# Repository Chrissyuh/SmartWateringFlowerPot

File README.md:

# Self-Watering Flower Pot V2

Custom ESP32-S3 controller hardware and bring-up firmware for a self-watering flower pot prototype.

This repository contains the KiCad design files, generated fabrication outputs, mechanical STEP exports, board renders, BOM notes, bring-up reports, and the first safe test firmware used on the assembled Board A prototype.

## Current Status

- Board A cost-down prototype has been fabricated and hand assembled for bring-up.
- USB-C power, 3.3 V regulator, ESP32-S3 native USB flashing, status LEDs, moisture ADC, and pump-gate bring-up checks have been tested.
- Current firmware is a supervised pump-test build with adjustable manual pump pulses and a hard 2 second firmware maximum.
- Board B UI daughterboard files remain in the repository as a deferred optional design.
- The cost-down Board A fabrication package is available in `fabrication/board_a_cost_down/`.

## Hardware Overview

Board A is the main controller board:

- ESP32-S3-WROOM-1-N8 module
- USB-C 5 V input
- AP63203 buck regulator for the 3.3 V logic rail
- Capacitive soil moisture sensor input on `J3`
- AO3400A low-side pump MOSFET footprint with gate resistor and pulldown
- SS34-style pump flyback diode
- Red error LED and green status LED
- Optional reservoir switch and flow pulse pads
- Debug/programming backup header `J7`
- Test points for rails and key signals

Board B is a deferred UI daughterboard concept with OLED/encoder support.

## Firmware

The current bring-up firmware lives in `firmware/testcode1/`.

It hosts a local Wi-Fi access point and web page:

- SSID: `FlowerPot-testcode1`
- Password: `flowerpot1`
- URL: `http://192.168.4.1`

The page shows moisture ADC readings, rolling average, min/max/span, rough wetness band, collapsible charts, deep ESP diagnostics, optional input short status, flow pulse count, AP-client/session counters, Wi-Fi settings, LED test buttons, session JSON export, diagnostics JSON export, and a supervised adjustable pump test button. The firmware also prints USB serial UI hints so the Windows helper in `firmware/testcode1/tools/` can open the best available UI URL from a data-cable connection.

Important safety rule: this is not autonomous watering firmware. The pump button requires a browser warning acknowledgement, and the firmware caps each pump run at 2000 ms.

## Repository Map

- `SmartWateringFlowerPot.kicad_pro`, `.kicad_sch`, `.kicad_pcb` - Board A KiCad project
- `board_b_ui/` - deferred UI board KiCad project
- `firmware/testcode1/` - PlatformIO bring-up firmware
- `docs/` - design notes, pinout, BOM notes, bring-up checklist, and hardening review
- `reports/` - saved ERC/DRC and audit reports
- `outputs/` - schematic PDFs, routing PDFs/SVGs, reference images, and 3D renders
- `fabrication/` - Gerbers, drill files, BOM CSVs, and fab zips
- `mechanical/` - STEP exports for enclosure/mechanical fit checks
- `CODEX_HANDOVER.md` - detailed project history and design context

## Bring-Up Notes

Before connecting a pump:

- Verify `+5V`, `+3V3`, and `GND`.
- Confirm there are no rail shorts.
- Confirm the ESP32 flashes over USB.
- Confirm `PUMP_GATE` remains LOW during boot/reset.
- Test the MOSFET gate with the pump disconnected.
- Use short, supervised pump tests only after the MOSFET and flyback diode are verified. Do not run the pump from a laptop USB port.

The moisture connector `J3` board order is:

```text
3V3  GND  SIG
```

The common capacitive sensor mapping is:

```text
VCC -> +3V3
GND -> GND
AOUT -> SIG
```

## Build Firmware

From `firmware/testcode1/`:

```powershell
python -m platformio run
python -m platformio run --target upload
```

The current `platformio.ini` targets the ESP32-S3 over `COM3`; change the port if your machine enumerates it differently.

## KiCad Checks

KiCad 9 is expected. If `kicad-cli` is on your PATH:

```powershell
kicad-cli sch erc --format report --output reports/erc.txt SmartWateringFlowerPot.kicad_sch
kicad-cli pcb drc --format report --output reports/drc.txt SmartWateringFlowerPot.kicad_pcb
```

KiCad GUI remains the source of truth for visual PCB edits.

## License

This project is released under the MIT License. See `LICENSE`.

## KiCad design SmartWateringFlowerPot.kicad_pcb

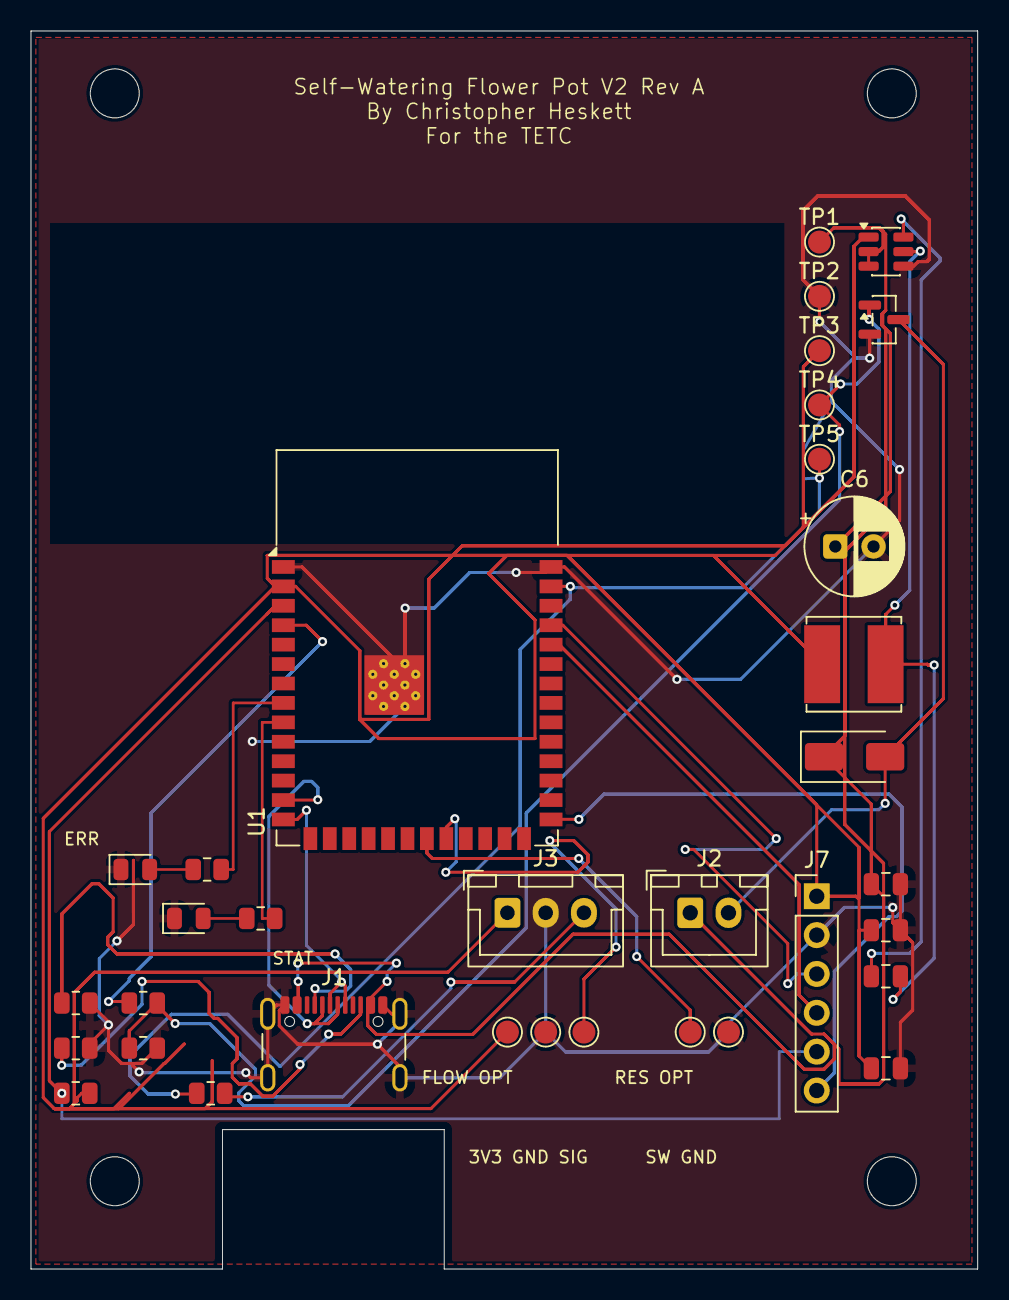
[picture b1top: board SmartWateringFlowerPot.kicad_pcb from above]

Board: 2 copper layers, 61.9 x 80.9 mm, 39 parts (1 on the bottom side), 24 nets.

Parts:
C1: 10uF 10V X7R input; C_0805_2012Metric
C2, C5: 22uF 6.3V X7R output; C_0805_2012Metric
C3: 100nF 10V BST; C_0805_2012Metric
C4: 100nF ADC filter DNP; C_0805_2012Metric
C6: 100uF 10V pump bulk; CP_Radial_D6.3mm_P2.50mm
D1: SS34 flyback; D_SMA
D2: ERROR red; LED_0805_2012Metric
D3: STATUS green; LED_0805_2012Metric
H1, H2, H3, H4: M3 mounting hole; MountingHole_3.2mm_M3
J1: USB-C 5V + USB2; USB_C_Receptacle_GCT_USB4105-xx-A_16P_TopMnt_Horizontal
J2: PUMP 5V; JST_XH_B2B-XH-A_1x02_P2.50mm_Vertical
J3: MOISTURE; JST_XH_B3B-XH-A_1x03_P2.50mm_Vertical
J7: DEBUG 3V3/GND/TX/RX/EN/BOOT; PinHeader_1x06_P2.54mm_Vertical
L1: 3.9uH shielded >=3A Isat; L_Bourns_SRN6045TA
Q1: AO3400A; SOT-23
R1: 5.1k CC1; R_0805_2012Metric
R2: 5.1k CC2; R_0805_2012Metric
R3: 10k EN pullup; R_0805_2012Metric
R4: 220R gate; R_0805_2012Metric
R5: 100k pulldown; R_0805_2012Metric
R10: 1k ADC series; R_0805_2012Metric
R11: 330R error LED; R_0805_2012Metric
R12: 330R status LED; R_0805_2012Metric
TP1: +5V TP; TestPoint_Pad_D1.5mm
TP2: GND TP; TestPoint_Pad_D1.5mm
TP3: +3V3 TP; TestPoint_Pad_D1.5mm
TP4: PUMP_GATE TP; TestPoint_Pad_D1.5mm
TP5: MOISTURE_ADC TP; TestPoint_Pad_D1.5mm
TP6: RESERVOIR_SW optional pad; TestPoint_Pad_D1.5mm
TP7, TP9: OPT_GND pad; TestPoint_Pad_D1.5mm
TP8: OPT_3V3 pad; TestPoint_Pad_D1.5mm
TP10: FLOW_PULSE optional pad; TestPoint_Pad_D1.5mm
U1: ESP32-S3-WROOM-1-N8; ESP32-S3-WROOM-1
U2: AP63203WU-7; TSOT-23-6

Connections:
+3V3: C2.1, C5.1, J3.1, J7.1, L1.1, R3.2, TP3.1, TP8.1, U1.2 (3V3), U2.1 (FB)
+5V: C1.1, C6.1, D1.1 (K), J1.A4 (VBUS), J1.A9 (VBUS), J1.B4 (VBUS), J1.B9 (VBUS), J2.1, TP1.1, U2.2 (EN), U2.3 (IN)
/ERROR_LED: R11.1, U1.8 (IO15)
/ERR_LED_A: D2.2, R11.2
/FLOW_PULSE: TP10.1, U1.22 (IO14)
/RESERVOIR_SW: TP6.1, U1.21 (IO13)
/STATUS_LED: R12.1, U1.9 (IO16)
/STAT_LED_A: D3.2, R12.2
GND: C1.2, C2.2, C4.2, C5.2, C6.2, D2.1, D3.1, J1.A1 (GND), J1.A12 (GND), J1.B1 (GND), J1.B12 (GND), J1.S1 (SHIELD), J3.2, J7.2, Q1.2 (S), R1.2, R2.2, R5.2, TP2.1, TP7.1, TP9.1, U1.1 (GND), U1.40 (GND), U1.41 (GND), U2.4 (GND)
unnamed: D1.2 (A), J2.2, Q1.3 (D)
unnamed: J1.A5 (CC1), R1.1
unnamed: J1.B5 (CC2), R2.1
unnamed: J3.3, R10.2
unnamed: J7.3, U1.37 (TXD0)
unnamed: J7.4, U1.36 (RXD0)
unnamed: J7.5, R3.1, U1.3 (EN)
unnamed: J7.6, U1.27 (IO0)
unnamed: Q1.1 (G), R4.2, R5.1, TP4.1
unnamed: C4.1, R10.1, TP5.1, U1.39 (IO1)
unnamed: R4.1, U1.4 (IO4)
unnamed: J1.A6 (D+), J1.B6 (D+), U1.14 (USB_D+)
unnamed: J1.A7 (D-), J1.B7 (D-), U1.13 (USB_D-)
unnamed: C3.1, U2.6 (BST)
unnamed: C3.2, L1.2, U2.5 (SW)

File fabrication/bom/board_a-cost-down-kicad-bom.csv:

"Refs","Value","Footprint","Qty","DNP"
"C1","10uF 10V X7R input","Capacitor_SMD:C_0805_2012Metric","1",""
"C2","22uF 6.3V X7R output","Capacitor_SMD:C_0805_2012Metric","1",""
"C3","100nF 10V BST","Capacitor_SMD:C_0805_2012Metric","1",""
"C5","22uF 6.3V X7R output","Capacitor_SMD:C_0805_2012Metric","1",""
"C6","100uF 10V pump bulk","Capacitor_THT:CP_Radial_D6.3mm_P2.50mm","1",""
"D1","SS34 flyback","Diode_SMD:D_SMA","1",""
"D2","ERROR red","LED_SMD:LED_0805_2012Metric","1",""
"D3","STATUS green","LED_SMD:LED_0805_2012Metric","1",""
"J1","USB-C 5V + USB2","Connector_USB:USB_C_Receptacle_GCT_USB4105-xx-A_16P_TopMnt_Horizontal","1",""
"J2","PUMP 5V","Connector_JST:JST_XH_B2B-XH-A_1x02_P2.50mm_Vertical","1",""
"J3","MOISTURE","Connector_JST:JST_XH_B3B-XH-A_1x03_P2.50mm_Vertical","1",""
"J7","DEBUG 3V3/GND/TX/RX/EN/BOOT","Connector_PinHeader_2.54mm:PinHeader_1x06_P2.54mm_Vertical","1",""
"L1","3.9uH shielded >=3A Isat","Inductor_SMD:L_Bourns_SRN6045TA","1",""
"Q1","AO3400A","Package_TO_SOT_SMD:SOT-23","1",""
"R1","5.1k CC1","Resistor_SMD:R_0805_2012Metric","1",""
"R2","5.1k CC2","Resistor_SMD:R_0805_2012Metric","1",""
"R3","10k EN pullup","Resistor_SMD:R_0805_2012Metric","1",""
"R4","220R gate","Resistor_SMD:R_0805_2012Metric","1",""
"R5","100k pulldown","Resistor_SMD:R_0805_2012Metric","1",""
"R10","1k ADC series","Resistor_SMD:R_0805_2012Metric","1",""
"R11","330R error LED","Resistor_SMD:R_0805_2012Metric","1",""
"R12","330R status LED","Resistor_SMD:R_0805_2012Metric","1",""
"TP1","+5V TP","TestPoint:TestPoint_Pad_D1.5mm","1",""
"TP2","GND TP","TestPoint:TestPoint_Pad_D1.5mm","1",""
"TP3","+3V3 TP","TestPoint:TestPoint_Pad_D1.5mm","1",""
"TP4","PUMP_GATE TP","TestPoint:TestPoint_Pad_D1.5mm","1",""
"TP5","MOISTURE_ADC TP","TestPoint:TestPoint_Pad_D1.5mm","1",""
"U1","ESP32-S3-WROOM-1-N8","RF_Module:ESP32-S3-WROOM-1","1",""
"U2","AP63203WU-7","Package_TO_SOT_SMD:TSOT-23-6","1",""

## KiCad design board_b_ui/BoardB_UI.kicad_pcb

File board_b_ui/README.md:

# Board B UI Daughterboard

Board B connects to Board A J6 through J1 with the same pin order:

1. `+3V3`
2. `GND`
3. `SDA`
4. `SCL`
5. `ENC_A`
6. `ENC_B`
7. `ENC_SW`
8. `ERROR_LED`
9. `STATUS_LED`

The OLED header target is the common 4-pin SSD1306 I2C module order `GND`, `VCC/3V3`, `SCL`, `SDA`. Verify the actual module pin order before fabrication.

The PCB outline is 64 mm x 38 mm with M2.5 non-plated mounting holes. The front side is the user-facing panel with the OLED header/module outline, EC11 encoder footprint, error/status LEDs, and labels. The 9-pin JST-XH cable connector and the support R/C parts are on the back side.

Board B has explicit routed copper for every net plus front/back `GND` zones. Refill zones in KiCad with `B` after manual edits and rerun DRC before fabrication.

Current review/fabrication artifacts:

- Checks: `reports/erc-board-b-front-panel.txt`, `reports/drc-board-b-front-panel.txt`, and `reports/drc-board-b-front-panel-parity.txt`
- Routing review: `outputs/BoardB_UI_routing.svg` and `outputs/BoardB_UI_routing.pdf`
- Schematic PDF: `outputs/BoardB_UI_schematic.pdf`
- STEP: `mechanical/BoardB_UI.step`
- Gerbers and drills: `../fabrication/board_b/`

The KiCad footprint references an EC11 3D model under `Rotary_Encoder.3dshapes`. This KiCad install does not include that model, so the STEP export may omit the encoder body even though the footprint, holes, and courtyard are present.

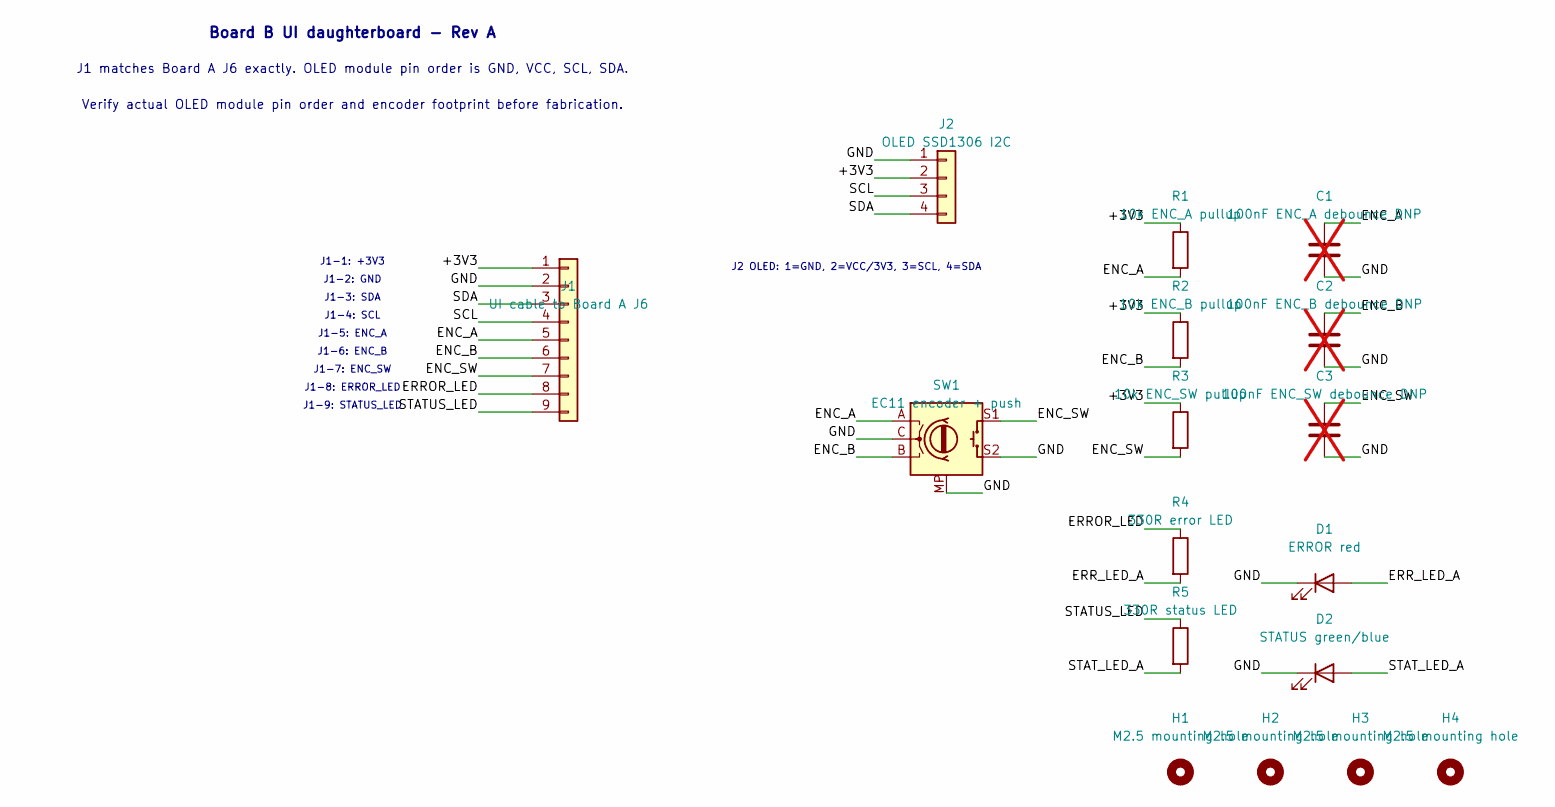
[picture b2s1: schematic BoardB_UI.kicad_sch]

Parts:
C1: 100nF ENC_A debounce DNP; C_0805_2012Metric; not fitted
C2: 100nF ENC_B debounce DNP; C_0805_2012Metric; not fitted
C3: 100nF ENC_SW debounce DNP; C_0805_2012Metric; not fitted
D1: ERROR red; LED_0805_2012Metric
D2: STATUS green/blue; LED_0805_2012Metric
H1, H2, H3, H4: M2.5 mounting hole; MountingHole_2.7mm_M2.5
J1: UI cable to Board A J6; JST_XH_S9B-XH-A_1x09_P2.50mm_Horizontal
J2: OLED SSD1306 I2C; PinHeader_1x04_P2.54mm_Vertical
R1: 10k ENC_A pullup; R_0805_2012Metric
R2: 10k ENC_B pullup; R_0805_2012Metric
R3: 10k ENC_SW pullup; R_0805_2012Metric
R4: 330R error LED; R_0805_2012Metric
R5: 330R status LED; R_0805_2012Metric
SW1: EC11 encoder + push; RotaryEncoder_Alps_EC11E-Switch_Vertical_H20mm

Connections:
/+3V3: J1.1, J2.2, R1.1, R2.1, R3.1
/ENC_A: C1.1, J1.5, R1.2, SW1.A
/ENC_B: C2.1, J1.6, R2.2, SW1.B
/ENC_SW: C3.1, J1.7, R3.2, SW1.S1
/ERROR_LED: J1.8, R4.1
/ERR_LED_A: D1.2 (A), R4.2
/GND: C1.2, C2.2, C3.2, D1.1 (K), D2.1 (K), J1.2, J2.1, SW1.C, SW1.MP, SW1.S2
/SCL: J1.4, J2.3
/SDA: J1.3, J2.4
/STATUS_LED: J1.9, R5.1
/STAT_LED_A: D2.2 (A), R5.2

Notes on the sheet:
Board B UI daughterboard - Rev A
J1 matches Board A J6 exactly. OLED module pin order is GND, VCC, SCL, SDA.
Verify actual OLED module pin order and encoder footprint before fabrication.
J1-1: +3V3
J1-2: GND
J1-3: SDA
J1-4: SCL
J1-5: ENC_A
J1-6: ENC_B
J1-7: ENC_SW
J1-8: ERROR_LED
J1-9: STATUS_LED
J2 OLED: 1=GND, 2=VCC/3V3, 3=SCL, 4=SDA

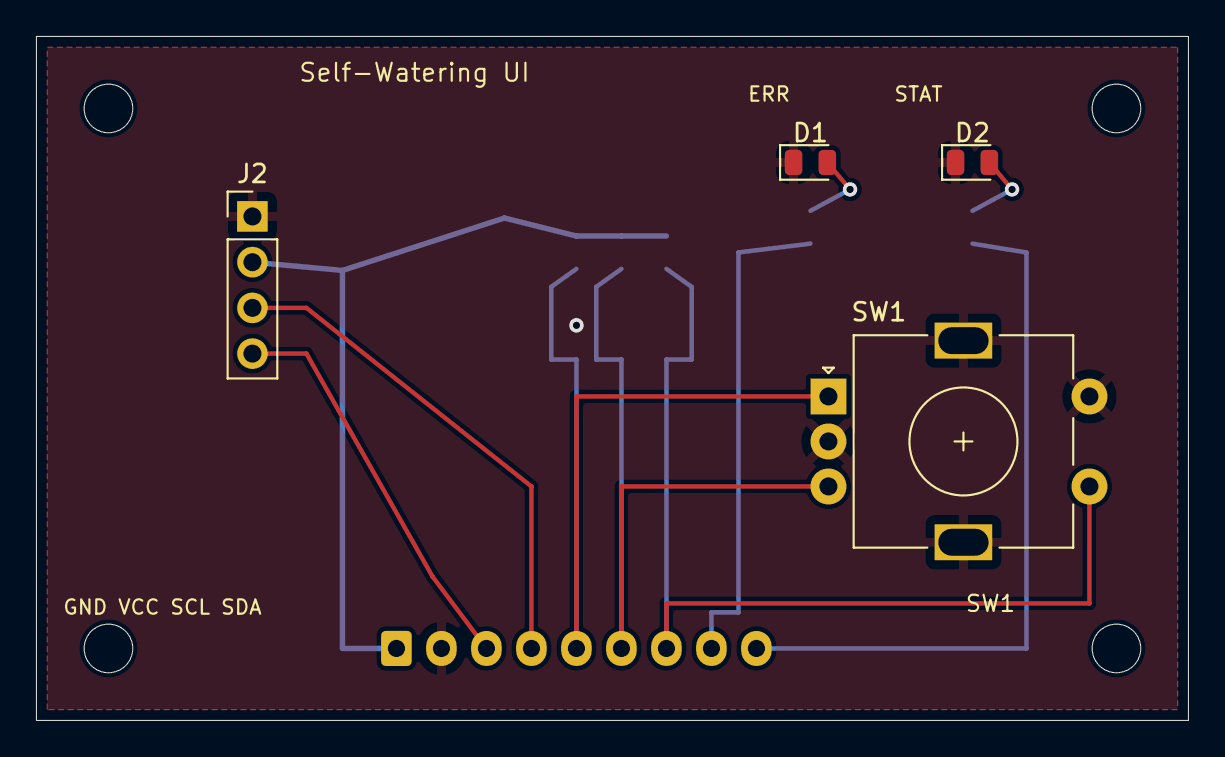
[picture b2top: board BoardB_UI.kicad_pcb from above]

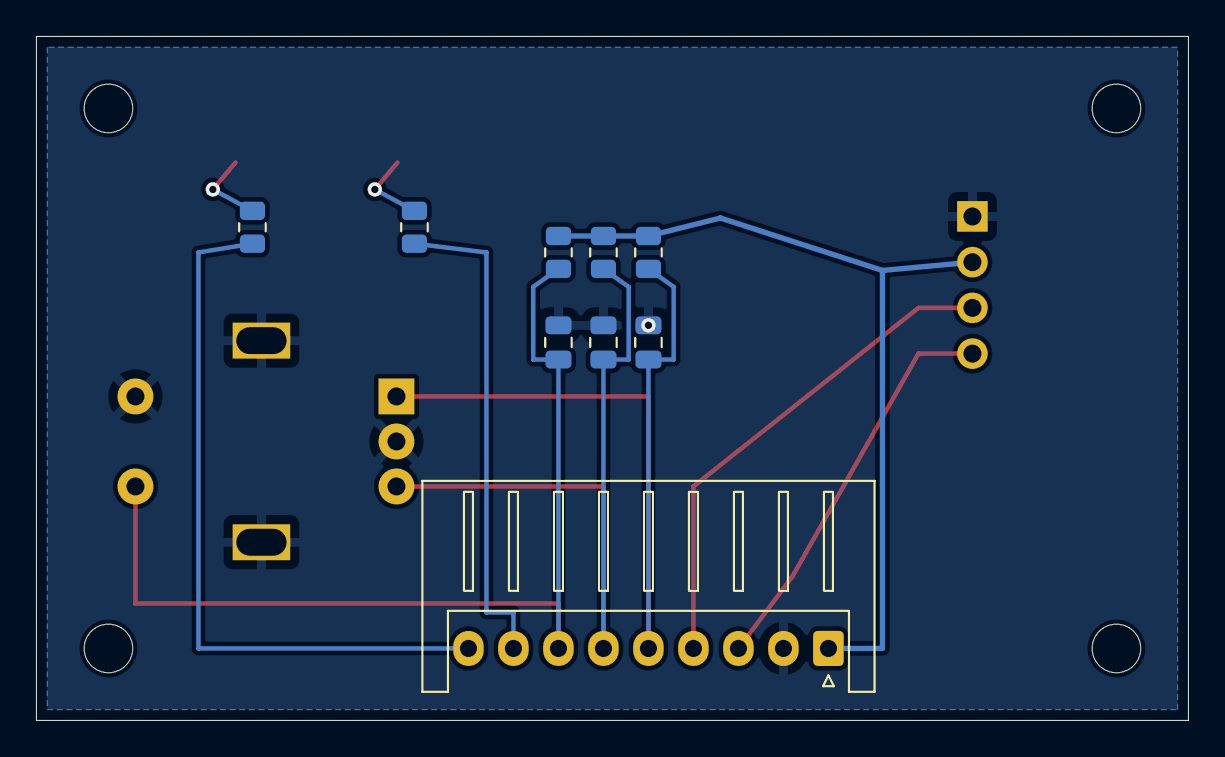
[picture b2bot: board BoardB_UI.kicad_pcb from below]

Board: 2 copper layers, 64.0 x 38.0 mm, 17 parts (9 on the bottom side), 11 nets.

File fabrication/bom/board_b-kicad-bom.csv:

"Refs","Value","Footprint","Qty","DNP"
"C1","100nF ENC_A debounce DNP","Capacitor_SMD:C_0805_2012Metric","1","DNP"
"C2","100nF ENC_B debounce DNP","Capacitor_SMD:C_0805_2012Metric","1","DNP"
"C3","100nF ENC_SW debounce DNP","Capacitor_SMD:C_0805_2012Metric","1","DNP"
"D1","ERROR red","LED_SMD:LED_0805_2012Metric","1",""
"D2","STATUS green/blue","LED_SMD:LED_0805_2012Metric","1",""
"J1","UI cable to Board A J6","Connector_JST:JST_XH_S9B-XH-A_1x09_P2.50mm_Horizontal","1",""
"J2","OLED SSD1306 I2C","Connector_PinHeader_2.54mm:PinHeader_1x04_P2.54mm_Vertical","1",""
"R1","10k ENC_A pullup","Resistor_SMD:R_0805_2012Metric","1",""
"R2","10k ENC_B pullup","Resistor_SMD:R_0805_2012Metric","1",""
"R3","10k ENC_SW pullup","Resistor_SMD:R_0805_2012Metric","1",""
"R4","330R error LED","Resistor_SMD:R_0805_2012Metric","1",""
"R5","330R status LED","Resistor_SMD:R_0805_2012Metric","1",""
"SW1","EC11 encoder + push","Rotary_Encoder:RotaryEncoder_Alps_EC11E-Switch_Vertical_H20mm","1",""

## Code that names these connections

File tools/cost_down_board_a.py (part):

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    additions = []
    # Name the reused GPIO nets and optional pad nets.
    additions += [
        label("ERROR_LED", 142.24, 111.76, 0),
        label("STATUS_LED", 142.24, 114.30, 0),
        label("RESERVOIR_SW", 130.81, 106.68, 0),
        label("FLOW_PULSE", 130.81, 109.22, 0),
    ]

    ids = {ref: u() for ref in ("R11", "D2", "R12", "D3", "TP6", "TP7", "TP8", "TP9", "TP10")}
    additions += [
        symbol_r("R11", "330R error LED", 175.26, 124.46, ids["R11"]),
        wire(175.26, 120.65, 170.18, 120.65),
        label("ERROR_LED", 170.18, 120.65, 180),
        wire(175.26, 128.27, 170.18, 128.27),
        label("ERR_LED_A", 170.18, 128.27, 180),
        symbol_led("D2", "ERROR red", 195.58, 128.27, ids["D2"]),
        wire(191.77, 128.27, 186.69, 128.27),
        label("GND", 186.69, 128.27, 180),
        wire(199.39, 128.27, 204.47, 128.27),
        label("ERR_LED_A", 204.47, 128.27, 0),
        symbol_r("R12", "330R status LED", 175.26, 139.70, ids["R12"]),
        wire(175.26, 135.89, 170.18, 135.89),
        label("STATUS_LED", 170.18, 135.89, 180),
        wire(175.26, 143.51, 170.18, 143.51),
        label("STAT_LED_A", 170.18, 143.51, 180),
        symbol_led("D3", "STATUS green", 195.58, 143.51, ids["D3"]),
        wire(191.77, 143.51, 186.69, 143.51),
        label("GND", 186.69, 143.51, 180),
        wire(199.39, 143.51, 204.47, 143.51),
        label("STAT_LED_A", 204.47, 143.51, 0),
        symbol_tp("TP6", "RESERVOIR_SW optional pad", 175.26, 154.94, ids["TP6"]),
        wire(170.18, 154.94, 165.10, 154.94),
        label("RESERVOIR_SW", 165.10, 154.94, 180),
        symbol_tp("TP7", "OPT_GND pad", 175.26, 162.56, ids["TP7"]),
        wire(170.18, 162.56, 165.10, 162.56),
        label("GND", 165.10, 162.56, 180),
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        label("GND", 195.58, 162.56, 180),
        symbol_tp("TP10", "FLOW_PULSE optional pad", 205.74, 170.18, ids["TP10"]),
        wire(200.66, 170.18, 195.58, 170.18),
        label("FLOW_PULSE", 195.58, 170.18, 180),
        (
            '\t(text "Cost-down Rev A: no local OLED/encoder UI. Reservoir and flow are optional pads; firmware defaults disabled."\n'
            "\t\t(at 121.92 167.64 0)\n"
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        },
    )
    remove_stale_cost_down_stubs(board)
    rename_net_items(board, "Net-(J4-Pin_1)", "/RESERVOIR_SW")
    rename_net_items(board, "Net-(J5-Pin_3)", "/FLOW_PULSE")
    set_pad_net(board, "U1", "8", "/ERROR_LED")
    set_pad_net(board, "U1", "9", "/STATUS_LED")
    for pad_no, net_name in {
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
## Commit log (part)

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2026-05-18 Set up Smart Pot V2 project docs
2026-05-18 Add first schematic draft
2026-05-18 Prepare schematic for PCB pass two
2026-05-18 Improve schematic reliability for PCB readiness
2026-05-18 Add Board B UI daughterboard
2026-05-18 Add Board B fab package and Board A hold report
2026-05-19 Clean up Board B front panel layout
2026-05-19 Add one-order readiness package
2026-05-19 Prepare clean order batch package
2026-05-19 Add pre-order hardening review
2026-05-19 Rebrand order package and add five-unit BOM
2026-05-19 Document BOM cost reduction options
2026-05-19 Implement board-a-only cost-down redesign
2026-05-20 Fix cost-down USB-C edge clearance
2026-05-31 Add Board A assembly reference PDF
2026-06-06 Add labeled Board A top view
2026-06-06 Add KiCad reference designator screenshot
2026-06-06 Add Board A testcode1 firmware
2026-06-07 Add Board A presentation renders
2026-06-08 Improve safe testcode1 sensor UI
2026-06-08 Prepare project for open source release
2026-06-09 Add capped pump test firmware
2026-06-10 Add USB serial UI launcher support
2026-06-15 Add firmware charts and session export
2026-06-16 Add deep ESP diagnostics firmware
